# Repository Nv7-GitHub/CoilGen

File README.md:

<div id="top"></div>

## **IMPORTANT BUG FIX REGARDING FIELD SCALE IN "plot_various_error_metrics" PLOT - PLEASE UPDATE!**

<!-- ABOUT THE PROJECT -->

The CoilGen Project is a community-based tool for the generation of coil Layouts within the MRI/NMR environment. It is based on a boundary element method and generates an interconnected non-overlapping wire-tracks on 3D support structures. The focus of this work is post processing.

The user must specify a target field (e.g., bz(x,y,z)=y for a constant gradient in the y-direction) and a surface mesh geometry (e.g., a cylinder defined in an .stl file). The code then generates a coil layout in the form of a non-overlapping, interconnected wire trace to achieve the desired field.

## pyCoilGen: A Python Implementation
The author has supported the creation of **pyCoilGen**, a translation of this CoilGen Project to Python. The code is available on [GitHub](https://github.com/kev-m/pyCoilGen) and
documentation is available on [ReadTheDocs](https://pycoilgen.readthedocs.io/).

A full description is given in the following publication: https://onlinelibrary.wiley.com/doi/10.1002/mrm.29294

<!-- GETTING STARTED -->
## Getting Started

Check the documentation to get started

### Installation

1. Download and extract the file of the CoilGen repository
2. Run one of the examples in the folder "Examples"

The project requires MATLAB and optionally FastHenry2 for calculation of the coil inductance.  The MATLAB version should not be older than 2020A.

### Flex PCB export for KiCad

Cylindrical coils can be built as rolled 2-layer flex PCBs:
- **Slit-cylinder design:** the coil is designed on a cylinder with an axial slit (`'create slit cylinder mesh'`), so no track crosses the seam of the rolled board.
- **Export:** `export_kicad_flex_pcb` writes a KiCad board with both layers in series, variable-width traces and design rules, so KiCad's DRC checks every turn.
- **Re-simulation:** `import_kicad_flex_pcb` reads the board back and re-simulates the manufactured copper with CoilGen. The result works with the plotting functions.

See [Documentation/KiCad_flex_PCB_export.md](Documentation/KiCad_flex_PCB_export.md). The examples are:
- `Examples/halbach_flex_pcb_gradient_set.m`, which designs, exports, checks and re-simulates a 3-axis gradient set for a small Halbach magnet;
- `Examples/view_flex_pcb_coils.m`, which shows that set in 3D;
- `Examples/check_flex_pcb_boards.m`, which runs the independent board checks (KiCad DRC, same-net clearance, manufacturer limits, full-width field).

Manufacturer stackups and limits are kept as JSON profiles in `KiCad_flex_PCBs/fab_profiles/` (JLCPCB 2-layer flex, 1 oz, 0.2 mm for the example). Each board also has a STEP model of the rolled board (`<coil>.step.zip`: board, copper and silkscreen as separate colored bodies) made with `export_rolled_step`. Regenerate it whenever the board changes.

### Algorithm overview

<!-- LICENSE -->
## License

 See `LICENSE.txt` for more information.

<p align="right">(<a href="#top">back to top</a>)</p>

<!-- CONTACT -->
## Contact

Philipp Amrein, Github User: Philipp-MR 

Project Link: [https://github.com/Philipp-MR/CoilGen]

<p align="right">(<a href="#top">back to top</a>)</p>

## Citation

For citation of this work, please refer to the following publication:
https://onlinelibrary.wiley.com/doi/10.1002/mrm.29294
https://doi.org/10.1002/mrm.29294

<p align="right">(<a href="#top">back to top</a>)</p>

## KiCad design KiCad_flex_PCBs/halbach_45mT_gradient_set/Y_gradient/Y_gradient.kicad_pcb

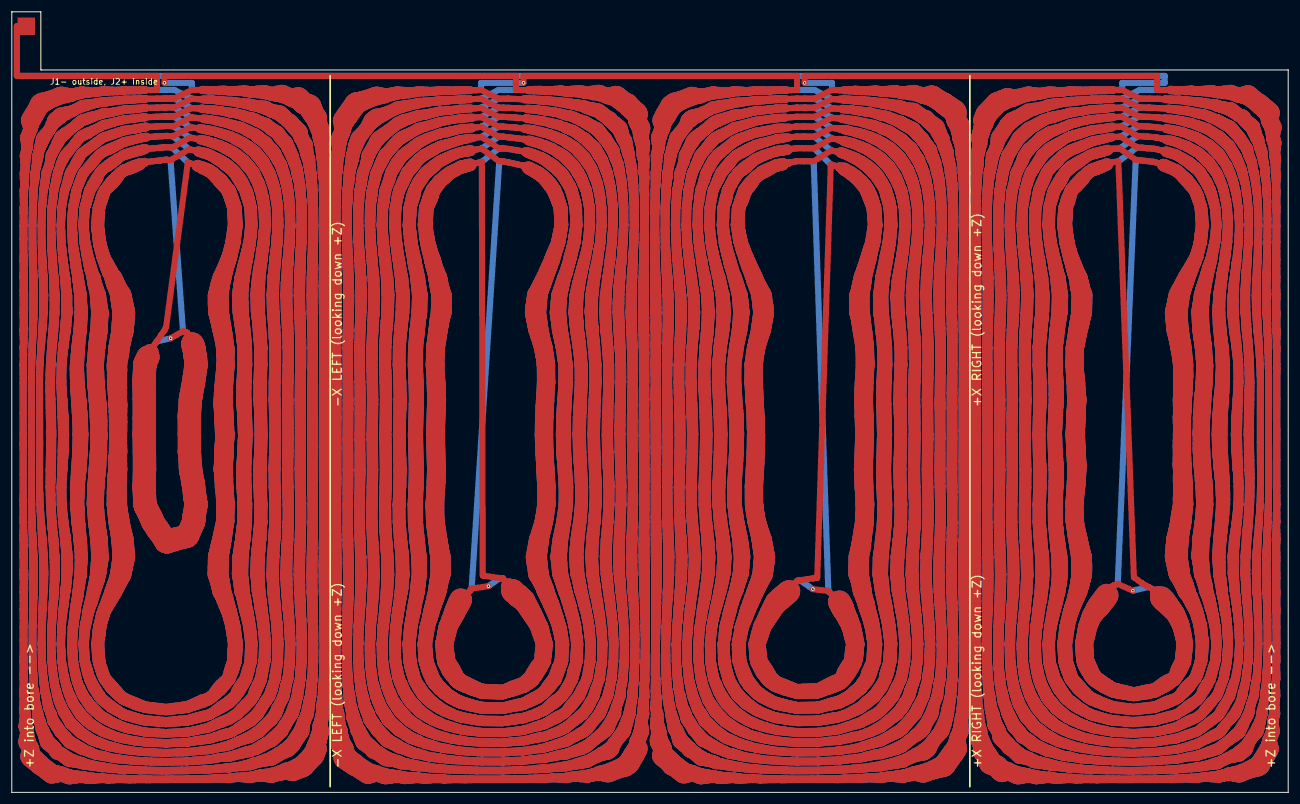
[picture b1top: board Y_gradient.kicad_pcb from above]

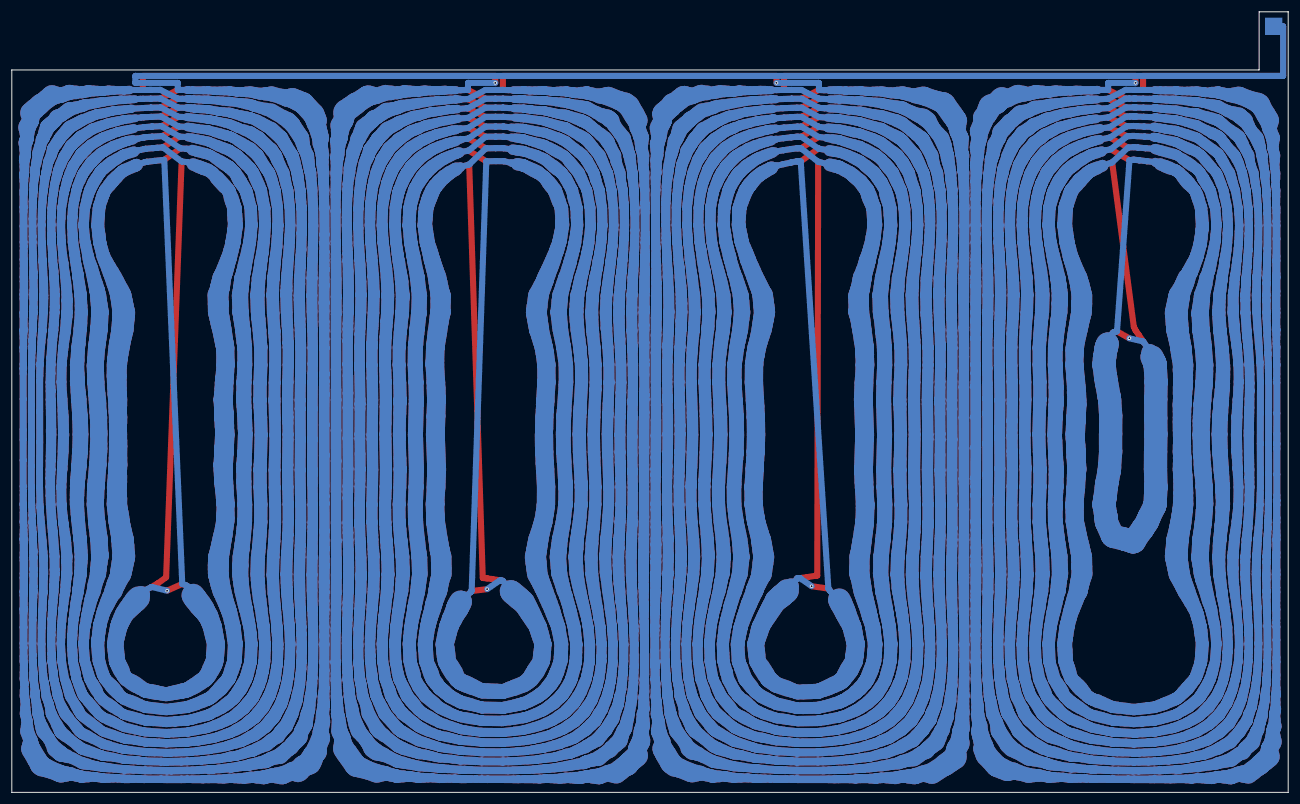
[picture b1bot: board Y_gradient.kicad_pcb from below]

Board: 2 copper layers, 219.4 x 134.2 mm, 70 parts (33 on the bottom side), 69 nets.

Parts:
J1-, J2+: SolderPad
NT1, NT2, NT3, NT4, NT5, NT6, NT7, NT8, NT9, NT10, NT11, NT12, NT13, NT14, NT15, NT16, NT17, NT18, NT19, NT20, NT21, NT22, NT23, NT24, NT25, NT26, NT27, NT28, NT29, NT30, NT31, NT32, NT33, NT34, NT35, NT36, NT37, NT38, NT39, NT40, NT41, NT42, NT43, NT44, NT45, NT46, NT47, NT48, NT49, NT50, NT51, NT52, NT53, NT54, NT55, NT56, NT57, NT58, NT59, NT60, NT61, NT62, NT63, NT64, NT65, NT66, NT67, NT68: NetTie; NetTie_Turn

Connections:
COIL_A: J1-.1, NT1.1
G1_B1: NT17.2, NT18.1
G1_B2: NT16.2, NT17.1
G1_B3: NT15.2, NT16.1
G1_B4: NT14.2, NT15.1
G1_B5: NT13.2, NT14.1
G1_B6: NT12.2, NT13.1
G1_B7: NT11.2, NT12.1
G1_B8: NT10.2, NT11.1
G1_T1: NT1.2, NT2.1
G1_T2: NT2.2, NT3.1
G1_T3: NT3.2, NT4.1
G1_T4: NT4.2, NT5.1
G1_T5: NT5.2, NT6.1
G1_T6: NT6.2, NT7.1
G1_T7: NT7.2, NT8.1
G1_T8: NT8.2, NT9.1
G1_T9: NT9.2, NT10.1
G2_B1: NT34.2, NT35.1
G2_B2: NT33.2, NT34.1
G2_B3: NT32.2, NT33.1
G2_B4: NT31.2, NT32.1
G2_B5: NT30.2, NT31.1
G2_B6: NT29.2, NT30.1
G2_B7: NT28.2, NT29.1
G2_B8: NT27.2, NT28.1
G2_T1: NT18.2, NT19.1
G2_T2: NT19.2, NT20.1
G2_T3: NT20.2, NT21.1
G2_T4: NT21.2, NT22.1
G2_T5: NT22.2, NT23.1
G2_T6: NT23.2, NT24.1
G2_T7: NT24.2, NT25.1
G2_T8: NT25.2, NT26.1
G2_T9: NT26.2, NT27.1
G3_B1: NT51.2, NT52.1
G3_B2: NT50.2, NT51.1
G3_B3: NT49.2, NT50.1
G3_B4: NT48.2, NT49.1
G3_B5: NT47.2, NT48.1
G3_B6: NT46.2, NT47.1
G3_B7: NT45.2, NT46.1
G3_B8: NT44.2, NT45.1
G3_T1: NT35.2, NT36.1
G3_T2: NT36.2, NT37.1
G3_T3: NT37.2, NT38.1
G3_T4: NT38.2, NT39.1
G3_T5: NT39.2, NT40.1
G3_T6: NT40.2, NT41.1
G3_T7: NT41.2, NT42.1
G3_T8: NT42.2, NT43.1
G3_T9: NT43.2, NT44.1
G4_B1: J2+.1, NT68.2
G4_B2: NT67.2, NT68.1
G4_B3: NT66.2, NT67.1
G4_B4: NT65.2, NT66.1
G4_B5: NT64.2, NT65.1
G4_B6: NT63.2, NT64.1
G4_B7: NT62.2, NT63.1
G4_B8: NT61.2, NT62.1
G4_T1: NT52.2, NT53.1
G4_T2: NT53.2, NT54.1
G4_T3: NT54.2, NT55.1
G4_T4: NT55.2, NT56.1
G4_T5: NT56.2, NT57.1
G4_T6: NT57.2, NT58.1
G4_T7: NT58.2, NT59.1
G4_T8: NT59.2, NT60.1
G4_T9: NT60.2, NT61.1
